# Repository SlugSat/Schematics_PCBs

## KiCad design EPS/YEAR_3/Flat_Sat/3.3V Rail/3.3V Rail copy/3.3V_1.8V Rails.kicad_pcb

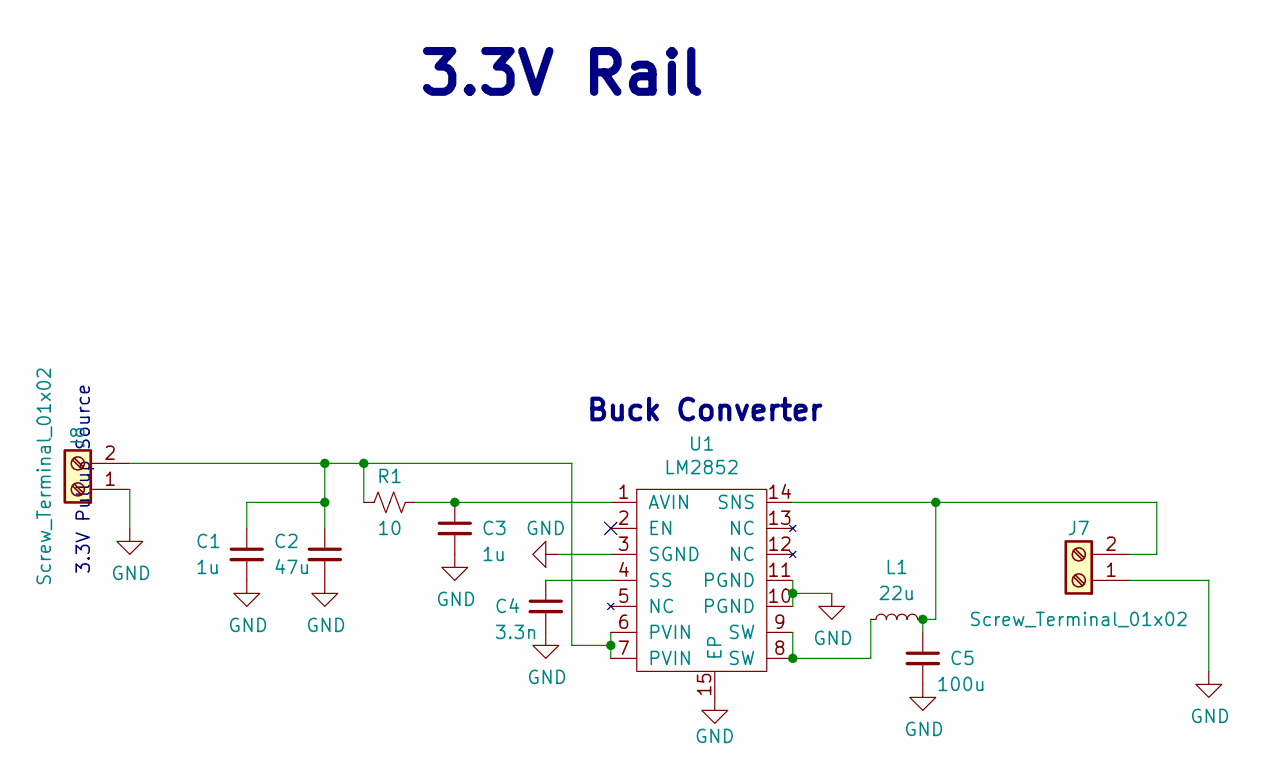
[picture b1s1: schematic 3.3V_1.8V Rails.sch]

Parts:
C1, C3: 1u; C_0805_2012Metric_Pad1.15x1.40mm_HandSolder
C2: 47u; C_0805_2012Metric_Pad1.15x1.40mm_HandSolder
C4: 3.3n; C_0805_2012Metric_Pad1.15x1.40mm_HandSolder
C5: 100u; C_0805_2012Metric_Pad1.15x1.40mm_HandSolder
J7, J8: Screw_Terminal_01x02; TerminalBlock_MetzConnect_Type094_RT03502HBLU_1x02_P5.00mm_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
L1: 22u; IND_SRP6540-100M
R1: 10; R_0805_2012Metric_Pad1.15x1.40mm_HandSolder
U1: LM2852

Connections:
GND: C1.2, C2.2, C3.2, C4.2, C5.2, J7.1, J8.1, U1.3 (SGND), U1.10 (PGND), U1.11 (PGND), U1.15 (EP)
unnamed: C1.1, C2.1, J8.2, R1.2, U1.6 (PVIN), U1.7 (PVIN)
unnamed: C3.1, R1.1, U1.1 (AVIN)
unnamed: C4.1, U1.4 (SS)
unnamed: C5.1, J7.2, L1.2, U1.14 (SNS)
unnamed: L1.1, U1.8 (SW), U1.9 (SW)

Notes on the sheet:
Buck Converter
3.3V Rail
3.3V Pullup Source

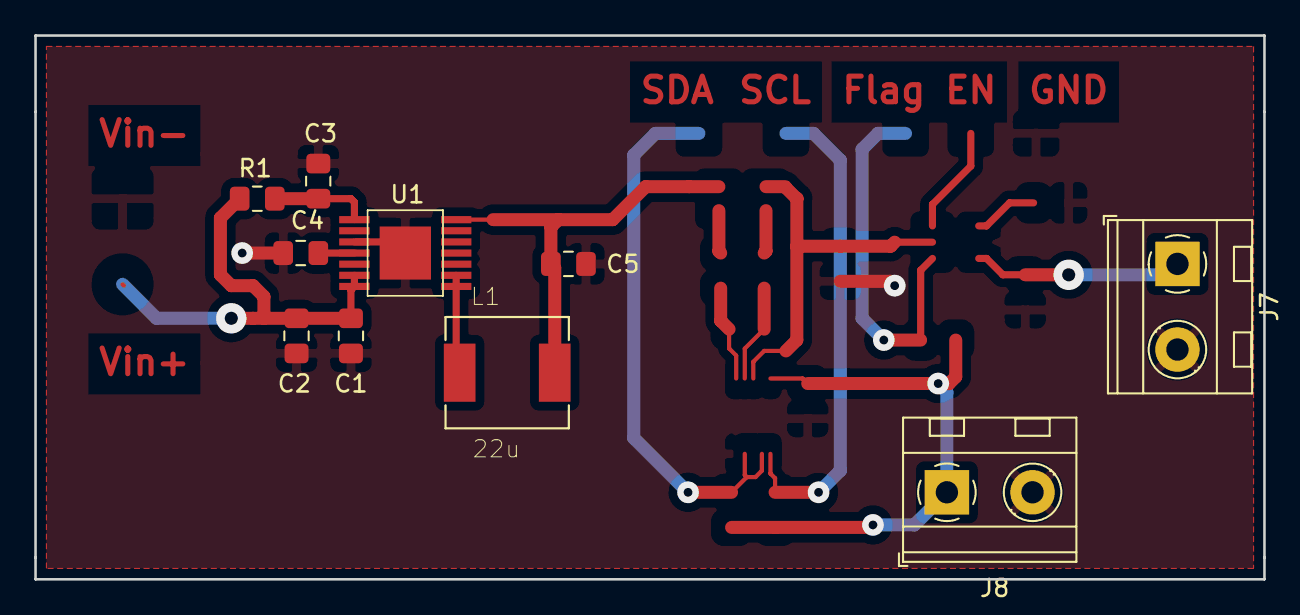
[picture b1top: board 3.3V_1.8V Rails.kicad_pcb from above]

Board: 2 copper layers, 71.8 x 31.8 mm, 10 parts (0 on the bottom side), 6 nets.

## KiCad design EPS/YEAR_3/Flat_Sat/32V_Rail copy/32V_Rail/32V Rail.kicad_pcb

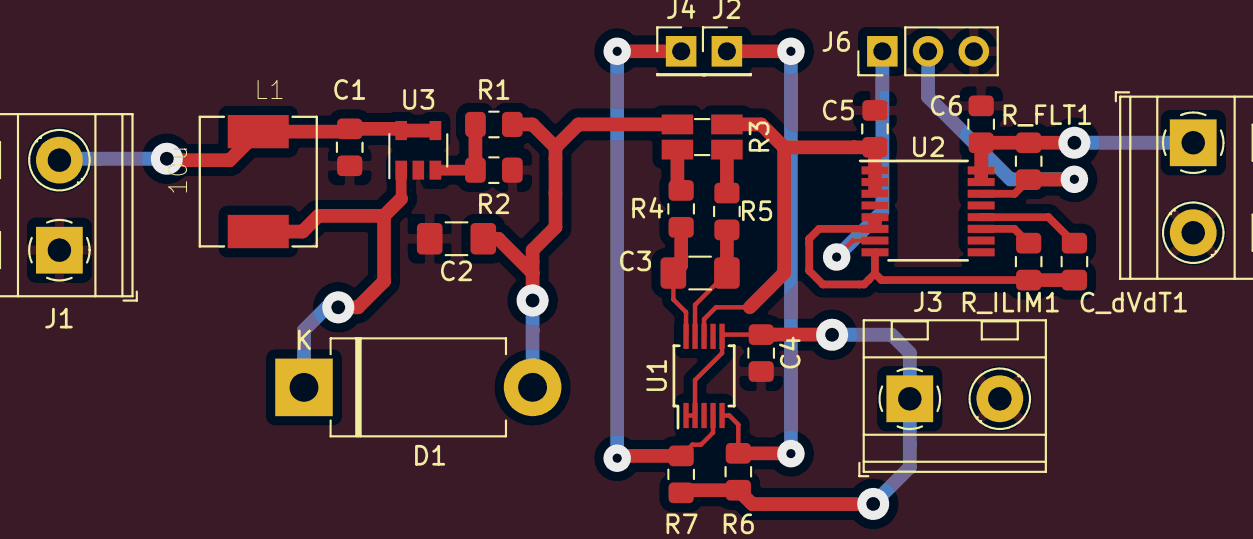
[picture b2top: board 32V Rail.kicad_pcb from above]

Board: 2 copper layers, 27 parts (0 on the bottom side), 19 nets.

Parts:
C1: 10u; C_0805_2012Metric_Pad1.15x1.40mm_HandSolder
C2: 47u; C_1206_3216Metric_Pad1.42x1.75mm_HandSolder
C3: 1u; C_1206_3216Metric_Pad1.42x1.75mm_HandSolder
C4: 0.1u; C_0805_2012Metric_Pad1.15x1.40mm_HandSolder
C5, C6: 1uF; C_0805_2012Metric_Pad1.15x1.40mm_HandSolder
C_dVdT1: 1uF; C_0805_2012Metric_Pad1.15x1.40mm_HandSolder
D1: DIODE; D_DO-201AD_P12.70mm_Horizontal
J1: Vin; TerminalBlock_MetzConnect_Type094_RT03502HBLU_1x02_P5.00mm_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
J2: SCL; PinHeader_1x01_P2.54mm_Vertical
J3: Supply Voltage; TerminalBlock_MetzConnect_Type094_RT03502HBLU_1x02_P5.00mm_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
J4: SDA; PinHeader_1x01_P2.54mm_Vertical
J5: Screw_Terminal_01x02; TerminalBlock_MetzConnect_Type094_RT03502HBLU_1x02_P5.00mm_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
J6: Conn_01x03_Male; PinHeader_1x03_P2.54mm_Vertical
L1: 10u; IND_SRP6540-100M
R1: 1.1M; R_0805_2012Metric_Pad1.15x1.40mm_HandSolder
R2: 43k; R_0805_2012Metric_Pad1.15x1.40mm_HandSolder
R3: 39m; R_Shunt_Ohmite_LVK12
R4, R5: 6.8; R_0805_2012Metric_Pad1.15x1.40mm_HandSolder
R6, R7: 20k; R_0805_2012Metric_Pad1.15x1.40mm_HandSolder
R_FLT1: 100k; R_0805_2012Metric_Pad1.15x1.40mm_HandSolder
R_ILIM1: 12k; R_0805_2012Metric_Pad1.15x1.40mm_HandSolder
U1: INA226; MSOP-10_3x3mm_P0.5mm
U2: TPS26600; TSSOP-16_4.4x5mm_P0.65mm
U3: MCP1663; SOT-23-5

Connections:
+3V3: C4.1, J3.1, R6.1, R7.2, U1.1, U1.2, U1.6
+BATT: C1.1, J1.2, L1.1, U3.4, U3.5
GND: C1.2, C2.2, C4.2, C5.2, C6.1, J1.1, J3.2, J5.2, J6.3, R2.2, U1.7, U2.4, U2.9, U2.13, U3.2
unnamed: C2.1, D1.2, R1.1, R3.4
unnamed: C3.1, R5.2, U1.9
unnamed: C3.2, R4.2, U1.10
unnamed: C5.1, R3.1, U1.8, U2.1, U2.2, U2.3
unnamed: C6.2, J5.1, R_FLT1.1, U2.15, U2.16
unnamed: C_dVdT1.1, R_ILIM1.2, U2.5, U2.6, U2.8
unnamed: C_dVdT1.2, U2.12
unnamed: D1.1, L1.2, U3.1
unnamed: J2.1, R6.2, U1.5
unnamed: J4.1, R7.1, U1.4
unnamed: J6.1, U2.7
unnamed: J6.2, R_FLT1.2, U2.14
unnamed: R1.2, R2.1, U3.3
unnamed: R3.2, R5.1
unnamed: R3.3, R4.1
unnamed: R_ILIM1.1, U2.11

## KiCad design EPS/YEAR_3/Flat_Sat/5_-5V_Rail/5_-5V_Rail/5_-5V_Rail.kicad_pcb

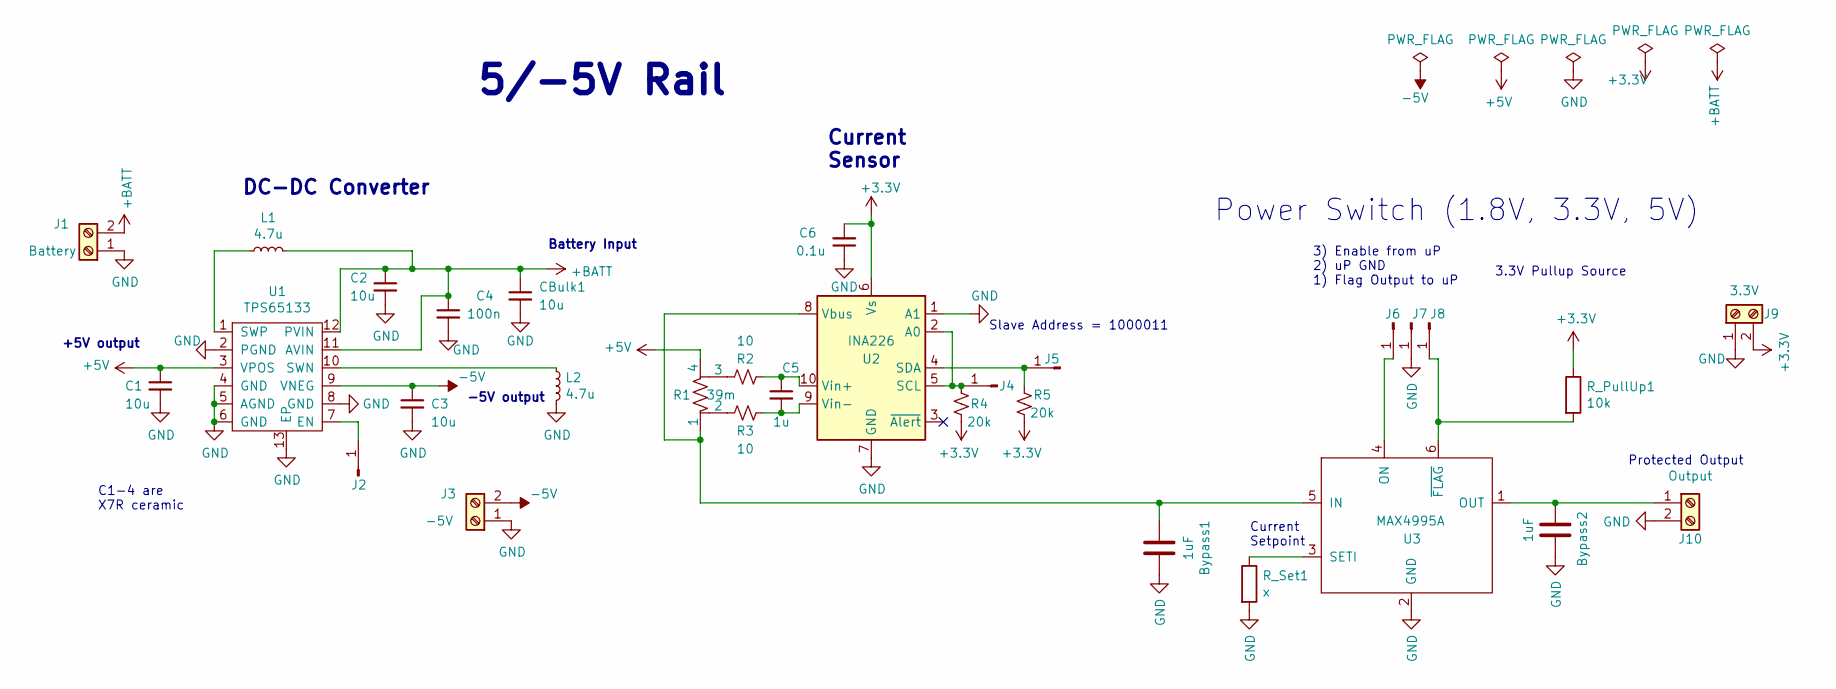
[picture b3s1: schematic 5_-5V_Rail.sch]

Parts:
Bypass1, Bypass2: 1uF; C_0805_2012Metric_Pad1.15x1.40mm_HandSolder
C1, C2, C3: 10u; C_0805_2012Metric_Pad1.15x1.40mm_HandSolder
C4: 100n; C_0805_2012Metric_Pad1.15x1.40mm_HandSolder
C5: 1u; C_0805_2012Metric_Pad1.15x1.40mm_HandSolder
C6: 0.1u; C_0805_2012Metric_Pad1.15x1.40mm_HandSolder
CBulk1: 10u; C_0805_2012Metric_Pad1.15x1.40mm_HandSolder
J1: Battery; TerminalBlock_MetzConnect_Type094_RT03502HBLU_1x02_P5.00mm_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
J2: Enable; PinHeader_1x01_P2.54mm_Vertical
J3: -5V; TerminalBlock_MetzConnect_Type094_RT03502HBLU_1x02_P5.00mm_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
J4: SCL; PinHeader_1x01_P2.54mm_Vertical
J5: SDA; PinHeader_1x01_P2.54mm_Vertical
J6: ON; PinSocket_1x01_P2.54mm_Vertical
J7: GND; PinSocket_1x01_P2.54mm_Vertical
J8: Flag; PinSocket_1x01_P2.54mm_Vertical
J9: 3.3V; TerminalBlock_MetzConnect_Type094_RT03502HBLU_1x02_P5.00mm_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
J10: Output; TerminalBlock_MetzConnect_Type094_RT03502HBLU_1x02_P5.00mm_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
L1, L2: 4.7u; IND_SRP6540-100M
R1: 39m; R_Shunt_Ohmite_LVK12
R2, R3: 10; R_0805_2012Metric_Pad1.15x1.40mm_HandSolder
R4, R5: 20k; R_0805_2012Metric_Pad1.15x1.40mm_HandSolder
R_PullUp1: 10k; R_0805_2012Metric_Pad1.15x1.40mm_HandSolder
R_Set1: x; R_0805_2012Metric_Pad1.15x1.40mm_HandSolder
U1: TPS65133
U2: INA226; MSOP-10_3x3mm_P0.5mm
U3: MAX4995A; SOT-23-6_Handsoldering

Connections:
+3V3: C6.2, J9.2, R4.1, R5.1, R_PullUp1.1, U2.6 (Vs)
+5V: C1.1, R1.4, U1.3 (VPOS)
+BATT: C2.1, C4.1, CBulk1.1, J1.2, L1.2, U1.11 (AVIN), U1.12 (PVIN)
-5V: C3.1, J3.2, U1.9 (VNEG)
GND: Bypass1.1, Bypass2.1, C1.2, C2.2, C3.2, C4.2, C6.1, CBulk1.2, J1.1, J3.1, J7.1, J9.1, J10.2, L2.2, R_Set1.2, U1.2 (PGND), U1.4 (GND), U1.5 (AGND), U1.6 (GND), U1.8 (GND), U1.13 (EP), U2.1 (A1), U2.7 (GND), U3.2 (GND)
unnamed: Bypass1.2, R1.1, U2.8 (Vbus), U3.5 (IN)
unnamed: Bypass2.2, J10.1, U3.1 (OUT)
unnamed: C5.1, R2.1, U2.10 (Vin+)
unnamed: C5.2, R3.1, U2.9 (Vin-)
unnamed: J2.1, U1.7 (EN)
unnamed: J4.1, R4.2, U2.2 (A0), U2.5 (SCL)
unnamed: J5.1, R5.2, U2.4 (SDA)
unnamed: J6.1, U3.4 (ON)
unnamed: J8.1, R_PullUp1.2, U3.6 (~FLAG)
unnamed: L1.1, U1.1 (SWP)
unnamed: L2.1, U1.10 (SWN)
unnamed: R1.2, R3.2
unnamed: R1.3, R2.2
unnamed: R_Set1.1, U3.3 (SETI)

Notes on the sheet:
Current Sensor
5/-5V Rail
DC-DC Converter
+5V output
-5V output
Battery Input
C1-4 are X7R ceramic
3) Enable from uP 2) uP GND 1) Flag Output to uP
Protected Output
3.3V Pullup Source
Power Switch (1.8V, 3.3V, 5V)
Current Setpoint
Slave Address = 1000011

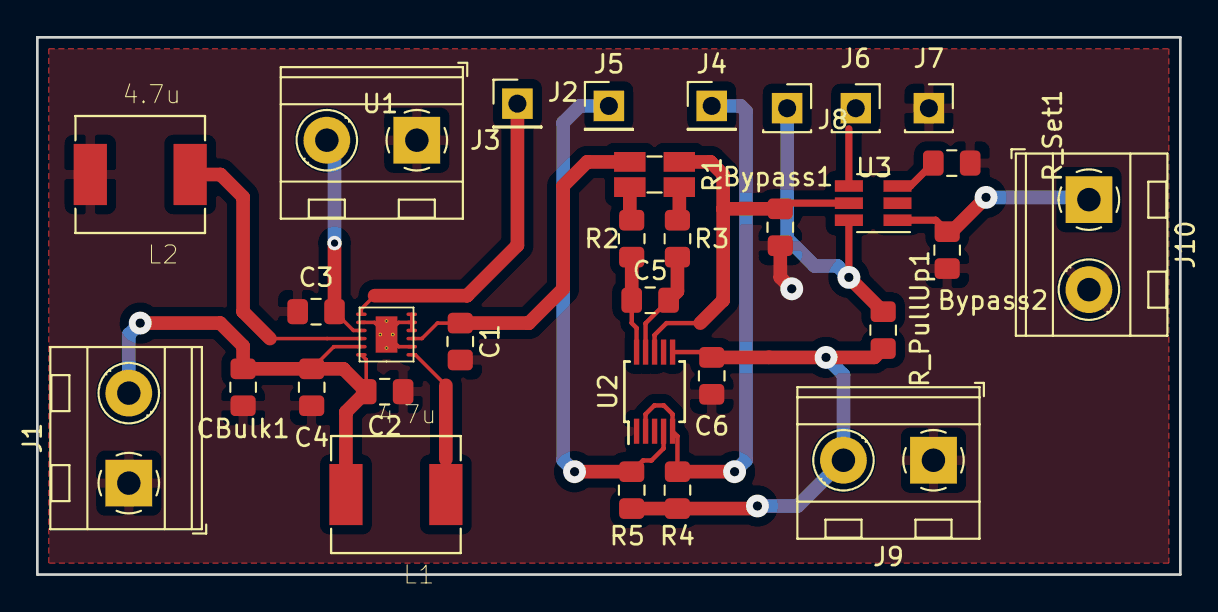
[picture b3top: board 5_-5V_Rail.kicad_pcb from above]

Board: 2 copper layers, 63.5 x 29.8 mm, 31 parts (0 on the bottom side), 19 nets.

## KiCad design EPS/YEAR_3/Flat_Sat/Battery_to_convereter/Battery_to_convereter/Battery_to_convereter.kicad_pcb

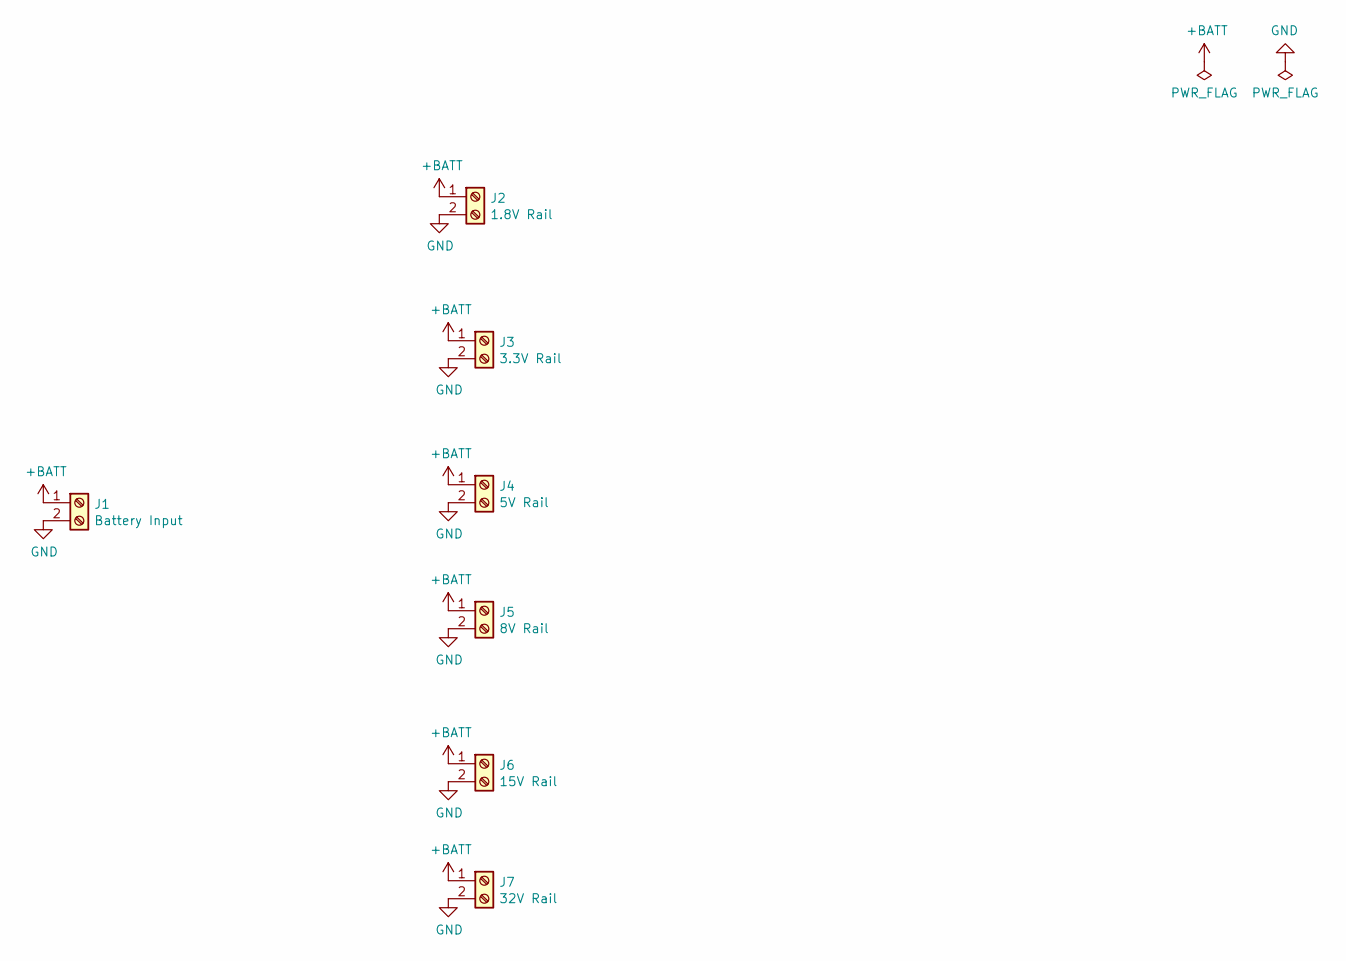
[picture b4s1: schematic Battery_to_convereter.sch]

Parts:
J1: Battery Input; TerminalBlock_MetzConnect_Type094_RT03502HBLU_1x02_P5.00mm_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
J2: 1.8V Rail; TerminalBlock_MetzConnect_Type094_RT03502HBLU_1x02_P5.00mm_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
J3: 3.3V Rail; TerminalBlock_MetzConnect_Type094_RT03502HBLU_1x02_P5.00mm_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
J4: 5V Rail; TerminalBlock_MetzConnect_Type094_RT03502HBLU_1x02_P5.00mm_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
J5: 8V Rail; TerminalBlock_MetzConnect_Type094_RT03502HBLU_1x02_P5.00mm_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
J6: 15V Rail; TerminalBlock_MetzConnect_Type094_RT03502HBLU_1x02_P5.00mm_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
J7: 32V Rail; TerminalBlock_MetzConnect_Type094_RT03502HBLU_1x02_P5.00mm_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

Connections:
+BATT: J1.1, J2.1, J3.1, J4.1, J5.1, J6.1, J7.1
GND: J1.2, J2.2, J3.2, J4.2, J5.2, J6.2, J7.2

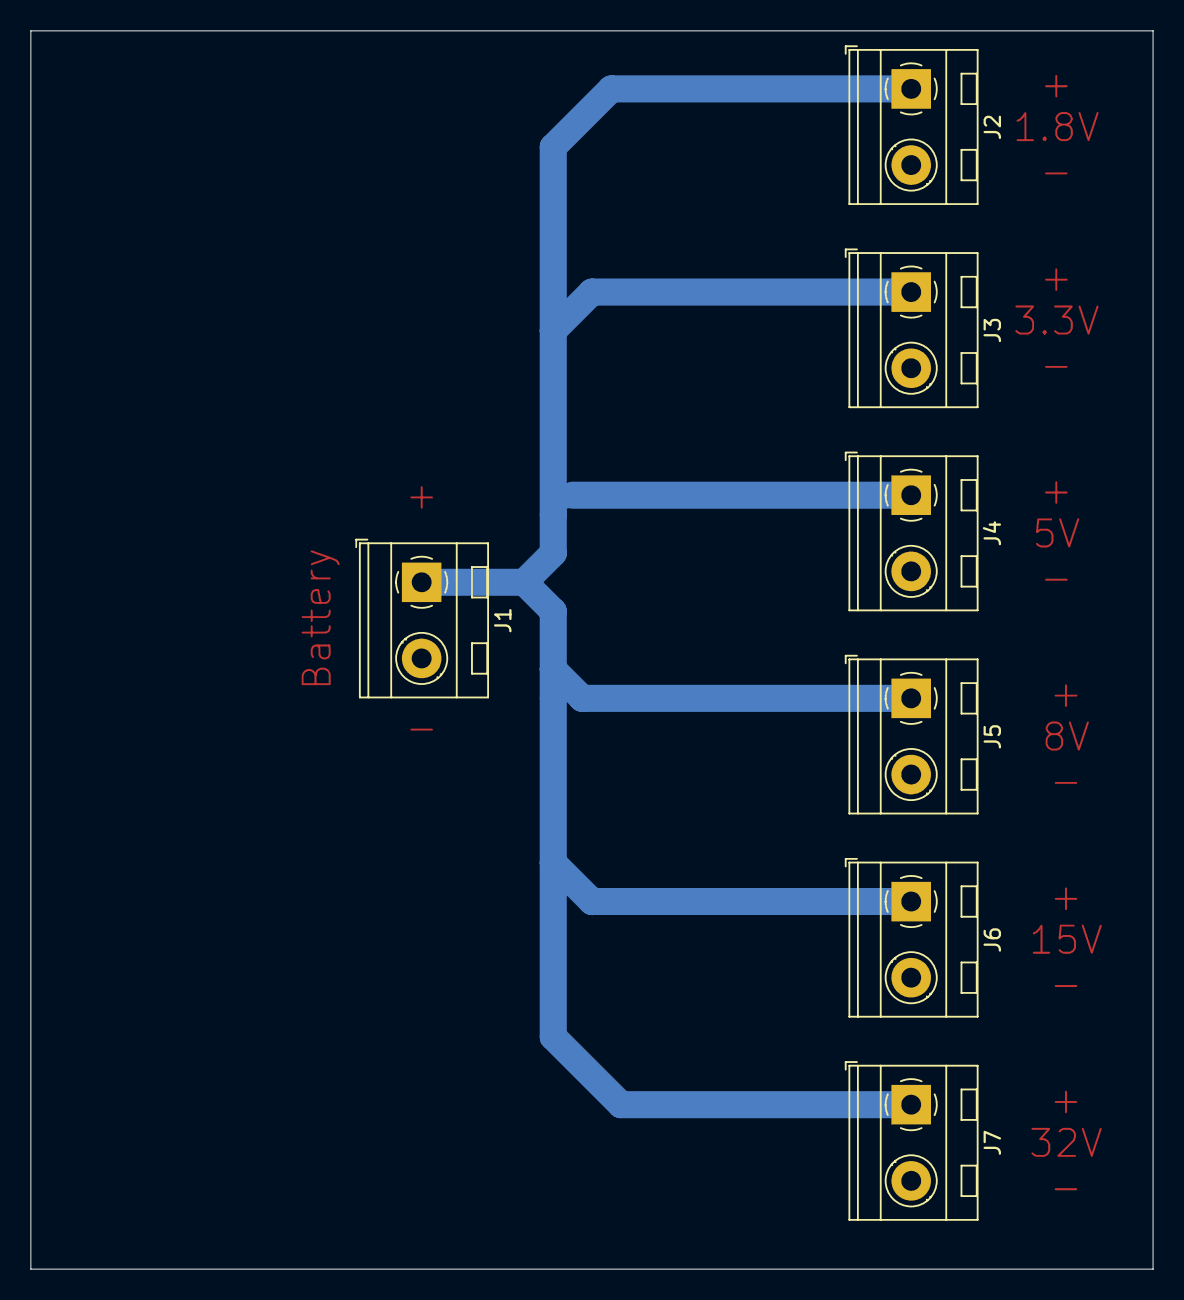
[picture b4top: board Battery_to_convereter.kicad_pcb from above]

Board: 2 copper layers, 73.7 x 81.3 mm, 7 parts (0 on the bottom side), 2 nets.

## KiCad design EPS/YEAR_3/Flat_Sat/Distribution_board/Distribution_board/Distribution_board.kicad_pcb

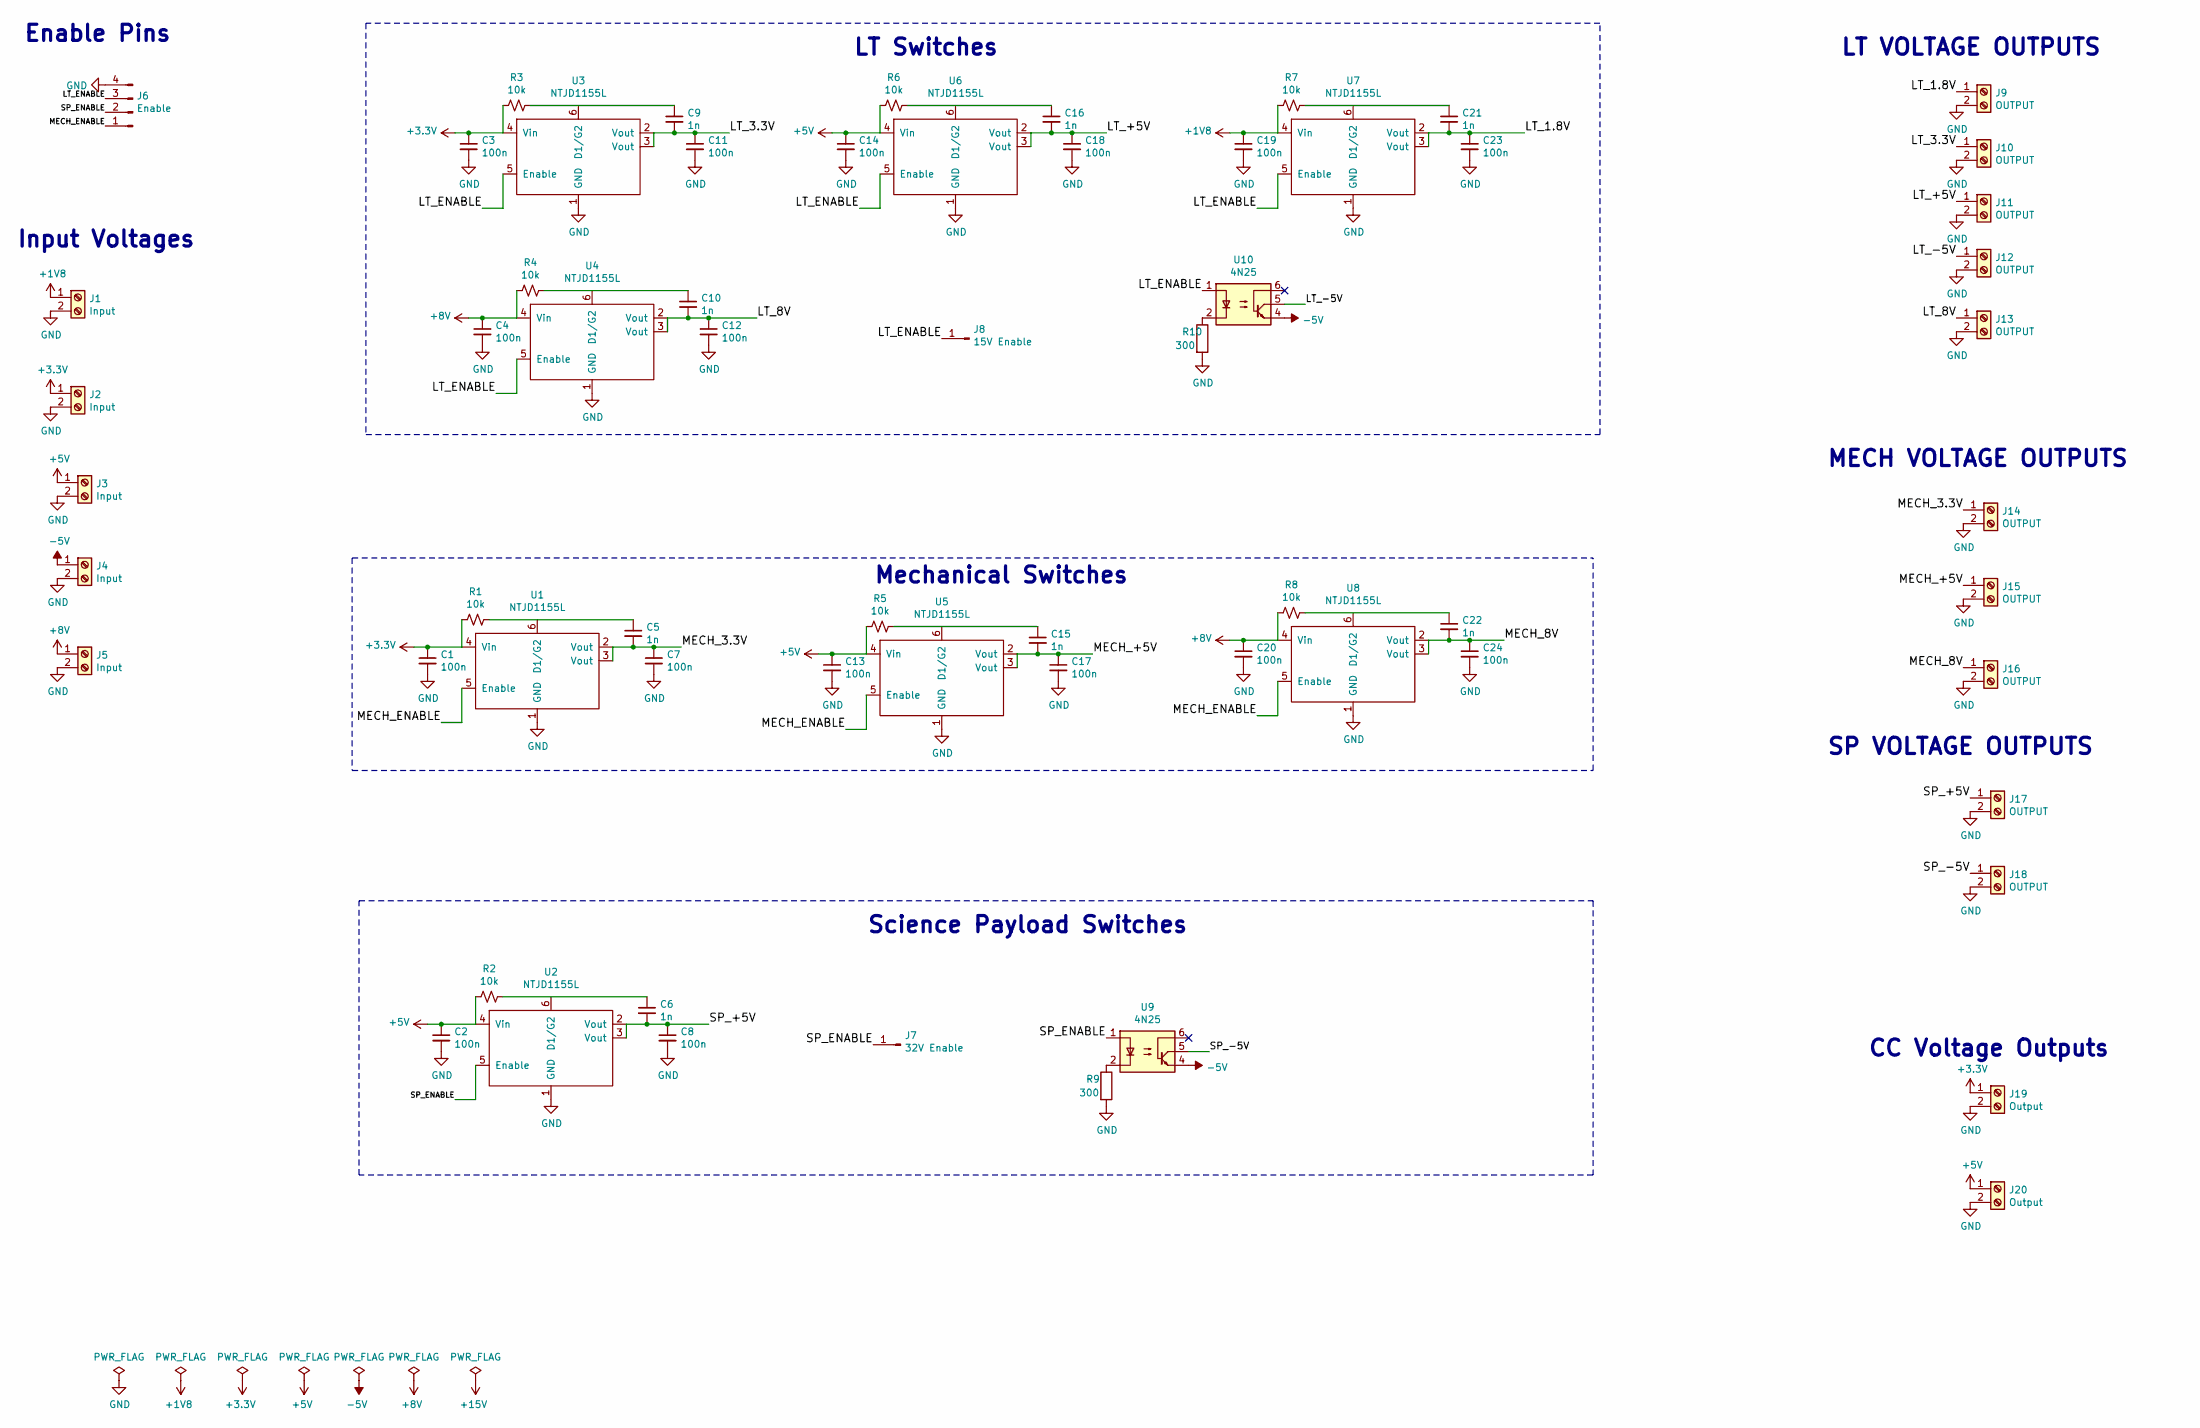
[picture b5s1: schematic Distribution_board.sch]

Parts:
C1, C2, C3, C4, C7, C8, C11, C12, C13, C14, C17, C18, C19, C20, C23, C24: 100n; C_0805_2012Metric_Pad1.15x1.40mm_HandSolder
C5, C6, C9, C10, C15, C16, C21, C22: 1n; C_0805_2012Metric_Pad1.15x1.40mm_HandSolder
J1, J2, J3, J4, J5: Input; TerminalBlock_MetzConnect_Type094_RT03502HBLU_1x02_P5.00mm_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
J6: Enable; PinSocket_1x04_P2.54mm_Vertical
J7: 32V Enable; PinHeader_1x01_P2.54mm_Vertical
J8: 15V Enable; PinHeader_1x01_P2.54mm_Vertical
J9, J10, J11, J12, J13, J14, J15, J16, J17, J18: OUTPUT; TerminalBlock_MetzConnect_Type094_RT03502HBLU_1x02_P5.00mm_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
J19, J20: Output; TerminalBlock_MetzConnect_Type094_RT03502HBLU_1x02_P5.00mm_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
R1, R2, R3, R4, R5, R6, R7, R8: 10k; R_0805_2012Metric_Pad1.15x1.40mm_HandSolder
R9, R10: 300; R_0805_2012Metric_Pad1.15x1.40mm_HandSolder
U1, U2, U3, U4, U5, U6, U7, U8: NTJD1155L; SOT-363_SC-70-6_Handsoldering
U9, U10: 4N25; DIP-6_W7.62mm

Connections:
+1V8: C19.1, J1.1, R7.2, U7.4 (Vin)
+3V3: C1.1, C3.1, J2.1, J19.1, R1.2, R3.2, U1.4 (Vin), U3.4 (Vin)
+5V: C2.1, C13.1, C14.1, J3.1, J20.1, R2.2, R5.2, R6.2, U2.4 (Vin), U5.4 (Vin), U6.4 (Vin)
+8V: C4.1, C20.1, J5.1, R4.2, R8.2, U4.4 (Vin), U8.4 (Vin)
-5V: J4.1, U9.4, U10.4
/LT_1.8V: C21.2, C23.1, J9.1, U7.2 (Vout), U7.3 (Vout)
/LT_3.3V: C9.2, C11.1, J10.1, U3.2 (Vout), U3.3 (Vout)
/LT_8V: C10.2, C12.1, J13.1, U4.2 (Vout), U4.3 (Vout)
/LT_+5V: C16.2, C18.1, J11.1, U6.2 (Vout), U6.3 (Vout)
/LT_-5V: J12.1, U10.5
/LT_ENABLE: J6.3, J8.1, U3.5 (Enable), U4.5 (Enable), U6.5 (Enable), U7.5 (Enable), U10.1
/MECH_3.3V: C5.2, C7.1, J14.1, U1.2 (Vout), U1.3 (Vout)
/MECH_8V: C22.2, C24.1, J16.1, U8.2 (Vout), U8.3 (Vout)
/MECH_+5V: C15.2, C17.1, J15.1, U5.2 (Vout), U5.3 (Vout)
/MECH_ENABLE: J6.1, U1.5 (Enable), U5.5 (Enable), U8.5 (Enable)
/SP_+5V: C6.2, C8.1, J17.1, U2.2 (Vout), U2.3 (Vout)
/SP_-5V: J18.1, U9.5
/SP_ENABLE: J6.2, J7.1, U2.5 (Enable), U9.1
GND: C1.2, C2.2, C3.2, C4.2, C7.2, C8.2, C11.2, C12.2, C13.2, C14.2, C17.2, C18.2, C19.2, C20.2, C23.2, C24.2, J1.2, J2.2, J3.2, J4.2, J5.2, J6.4, J9.2, J10.2, J11.2, J12.2, J13.2, J14.2, J15.2, J16.2, J17.2, J18.2, J19.2, J20.2, R9.2, R10.2, U1.1 (GND), U2.1 (GND), U3.1 (GND), U4.1 (GND), U5.1 (GND), U6.1 (GND), U7.1 (GND), U8.1 (GND)
unnamed: C5.1, R1.1
unnamed: C6.1, R2.1
unnamed: C9.1, R3.1
unnamed: C10.1, R4.1
unnamed: C15.1, R5.1
unnamed: C16.1, R6.1
unnamed: C21.1, R7.1
unnamed: C22.1, R8.1
unnamed: R9.1, U9.2
unnamed: R10.1, U10.2

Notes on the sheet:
CC Voltage Outputs
Mechanical Switches
LT VOLTAGE OUTPUTS
Science Payload Switches
MECH VOLTAGE OUTPUTS
SP VOLTAGE OUTPUTS
LT Switches
Enable Pins
Input Voltages

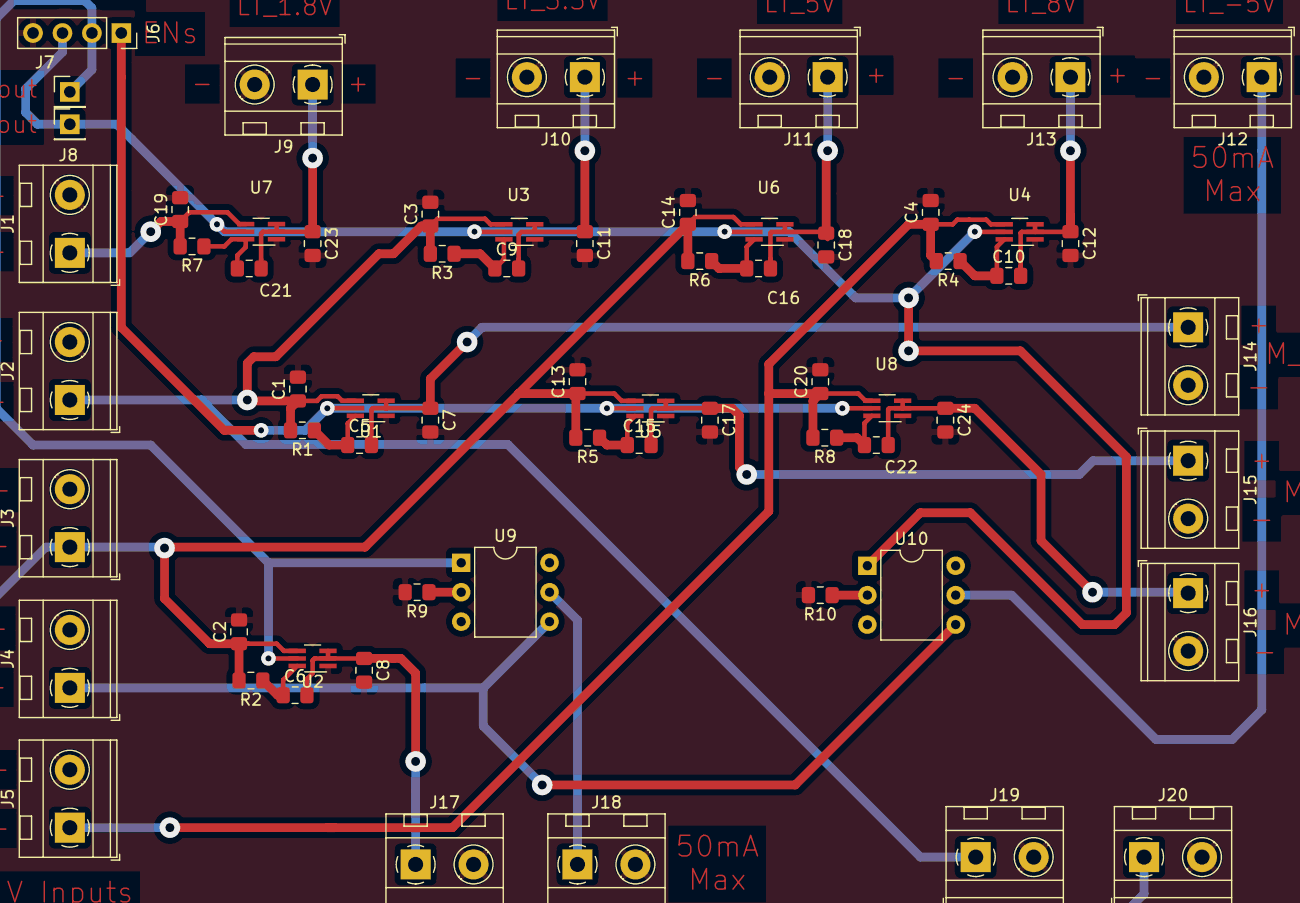
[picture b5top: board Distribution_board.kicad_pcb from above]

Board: 2 copper layers, 64 parts (0 on the bottom side), 29 nets.

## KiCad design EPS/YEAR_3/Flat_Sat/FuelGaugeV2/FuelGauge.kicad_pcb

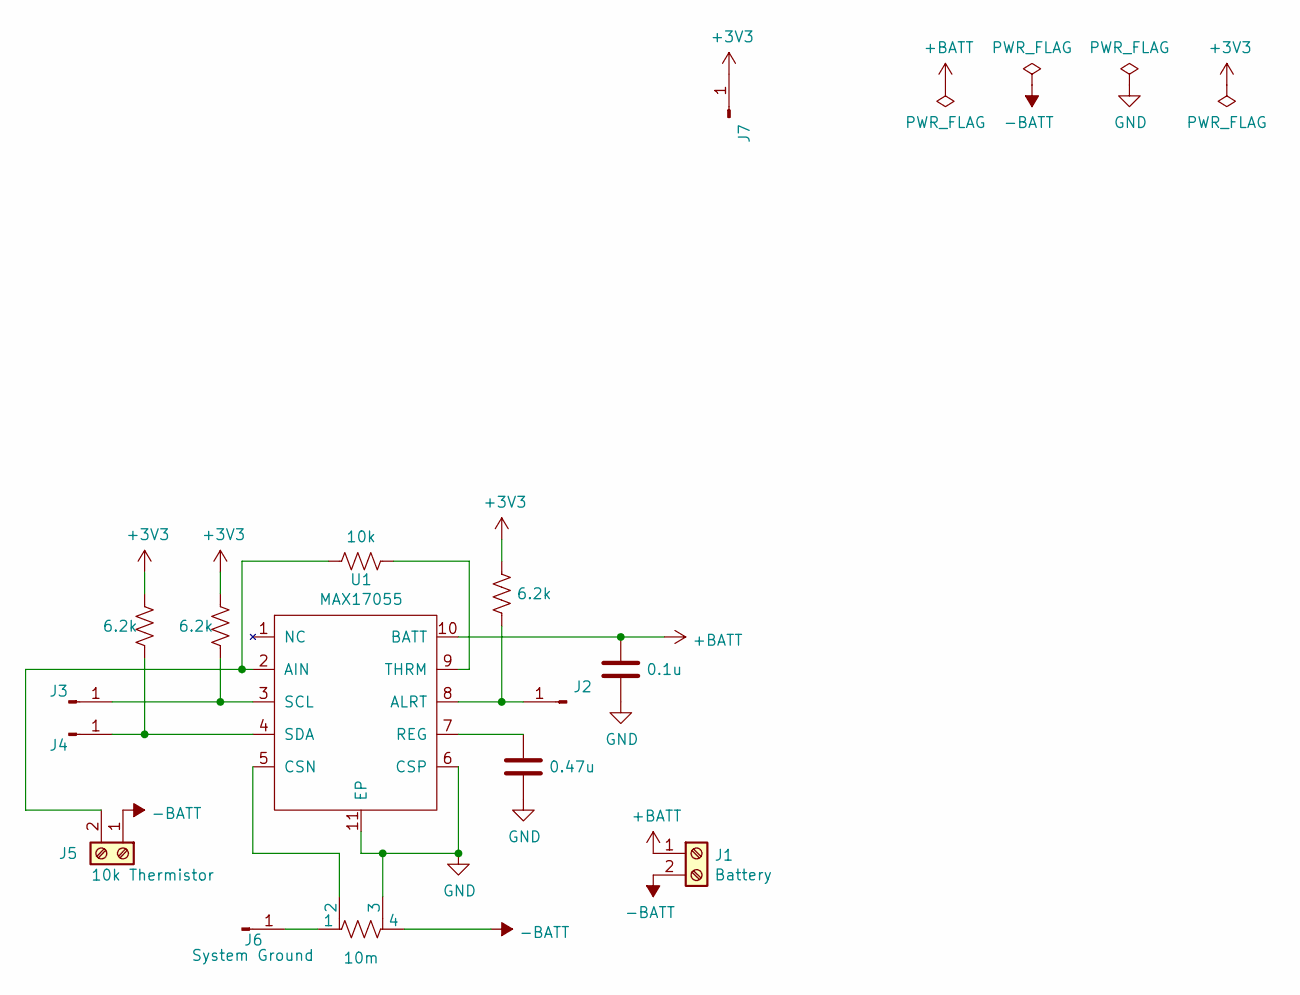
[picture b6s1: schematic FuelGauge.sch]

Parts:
C1: 0.1u; C_0805_2012Metric_Pad1.15x1.40mm_HandSolder
C2: 0.47u; C_0805_2012Metric_Pad1.15x1.40mm_HandSolder
J1: Battery; TerminalBlock_MetzConnect_Type094_RT03502HBLU_1x02_P5.00mm_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
J2: ALRT; PinHeader_1x01_P2.54mm_Vertical
J3: SCL; PinHeader_1x01_P2.54mm_Vertical
J4: SDA; PinHeader_1x01_P2.54mm_Vertical
J5: 10k Thermistor; TerminalBlock_MetzConnect_Type094_RT03502HBLU_1x02_P5.00mm_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
J6: System Ground; PinHeader_1x01_P2.54mm_Vertical
J7: 3.3V; PinHeader_1x01_P2.54mm_Vertical
R1, R3, R4: 6.2k; R_0805_2012Metric_Pad1.15x1.40mm_HandSolder
R2: 10k; R_0805_2012Metric_Pad1.15x1.40mm_HandSolder
R5: 10m; R_Shunt_Ohmite_LVK12
U1: MAX17055; 10-TDFN-EP

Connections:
+3V3: J7.1, R1.1, R3.1, R4.1
+BATT: C1.1, J1.1, U1.10 (BATT)
-BATT: J1.2, J5.1, R5.4
GND: C1.2, C2.2, R5.3, U1.6 (CSP), U1.11 (EP)
unnamed: C2.1, U1.7 (REG)
unnamed: J2.1, R1.2, U1.8 (ALRT)
unnamed: J3.1, R3.2, U1.3 (SCL)
unnamed: J4.1, R4.2, U1.4 (SDA)
unnamed: J5.2, R2.2, U1.2 (AIN)
unnamed: J6.1, R5.1
unnamed: R2.1, U1.9 (THRM)
unnamed: R5.2, U1.5 (CSN)

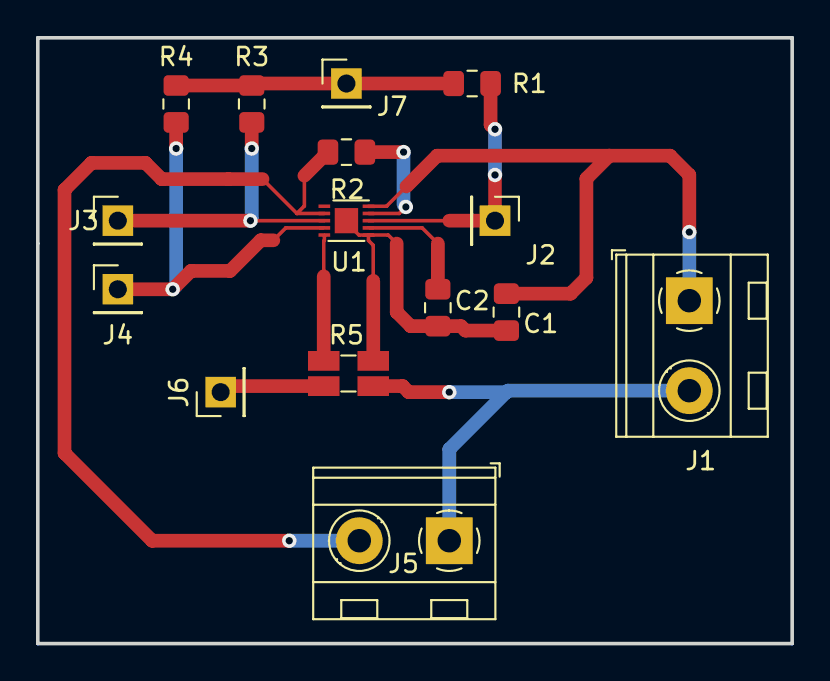
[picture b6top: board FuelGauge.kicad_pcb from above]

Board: 2 copper layers, 41.9 x 33.7 mm, 15 parts (0 on the bottom side), 12 nets.

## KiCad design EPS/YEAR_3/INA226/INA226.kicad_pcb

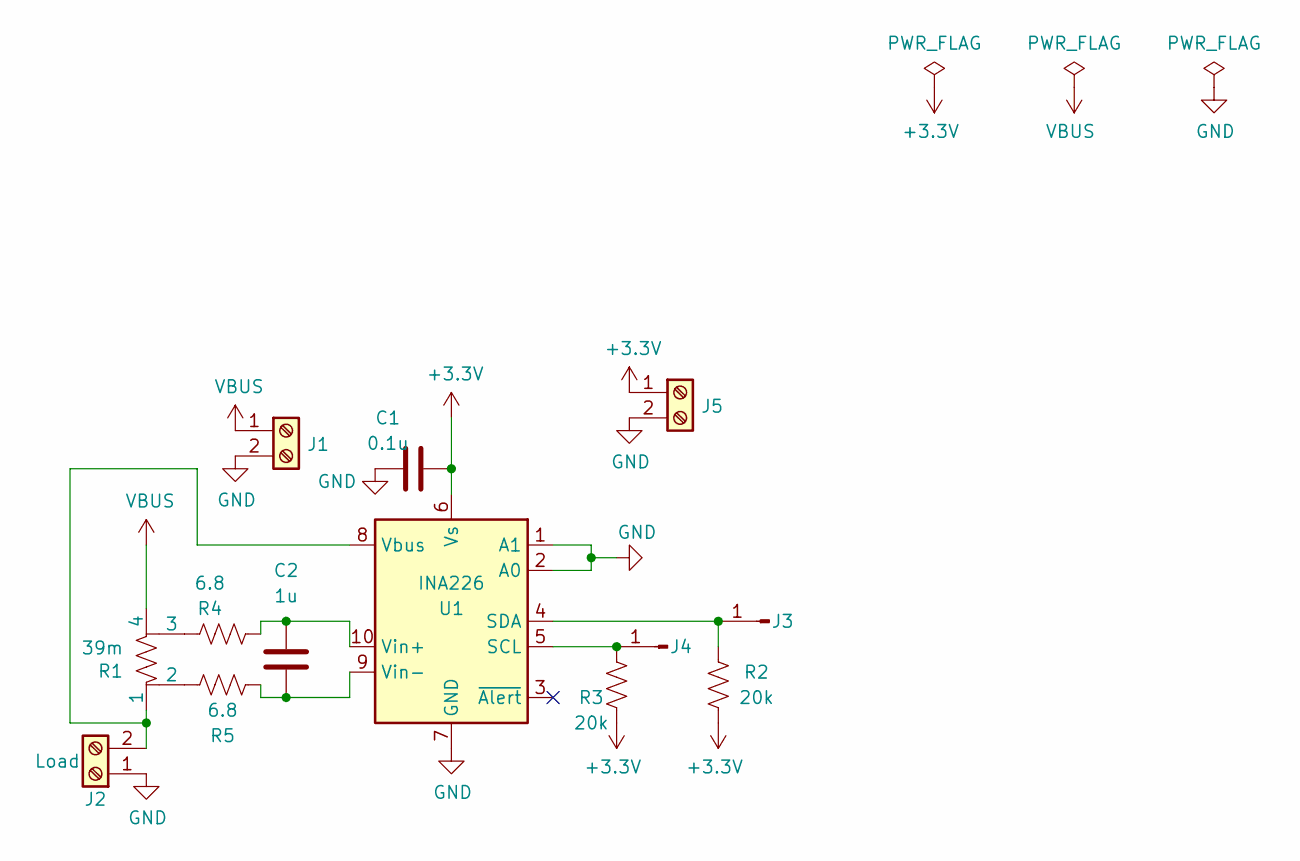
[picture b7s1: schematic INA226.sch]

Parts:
C1: 0.1u; C_0805_2012Metric_Pad1.15x1.40mm_HandSolder
C2: 1u; C_1206_3216Metric_Pad1.42x1.75mm_HandSolder
J1: Voltage Rail; TerminalBlock_MetzConnect_Type094_RT03502HBLU_1x02_P5.00mm_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
J2: Load; TerminalBlock_MetzConnect_Type094_RT03502HBLU_1x02_P5.00mm_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
J3: SDA; PinHeader_1x01_P2.54mm_Vertical
J4: SCL; PinHeader_1x01_P2.54mm_Vertical
J5: Supply Voltage; TerminalBlock_MetzConnect_Type094_RT03502HBLU_1x02_P5.00mm_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
R1: 39m; R_Shunt_Ohmite_LVK12
R2, R3: 20k; R_0805_2012Metric_Pad1.15x1.40mm_HandSolder
R4, R5: 6.8; R_0805_2012Metric_Pad1.15x1.40mm_HandSolder
U1: INA226; MSOP-10_3x3mm_P0.5mm

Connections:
+3V3: C1.1, J5.1, R2.2, R3.1, U1.6 (Vs)
GND: C1.2, J1.2, J2.1, J5.2, U1.1 (A1), U1.2 (A0), U1.7 (GND)
unnamed: C2.1, R5.2, U1.9 (Vin-)
unnamed: C2.2, R4.2, U1.10 (Vin+)
unnamed: J2.2, R1.1, U1.8 (Vbus)
unnamed: J3.1, R2.1, U1.4 (SDA)
unnamed: J4.1, R3.2, U1.5 (SCL)
unnamed: R1.2, R5.1
unnamed: R1.3, R4.1
VBUS: J1.1, R1.4

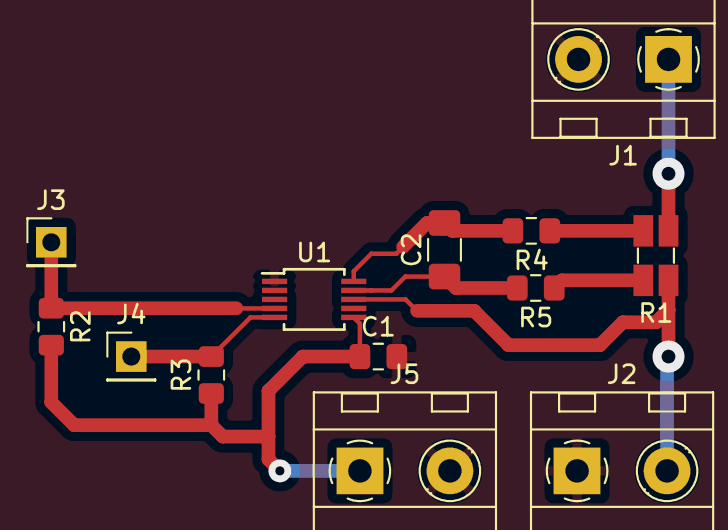
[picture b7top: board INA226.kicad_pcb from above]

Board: 2 copper layers, 13 parts (0 on the bottom side), 10 nets.
